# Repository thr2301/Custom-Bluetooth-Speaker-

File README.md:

# Bluetooth Speaker 

This repository contains the hardware design files and documentation for a custom Bluetooth Speaker circuit. The board integrates a lithium-ion battery management system, a boost converter, a Bluetooth audio receiver, and a Class-D audio amplifier into a single cohesive PCB. 

## Features

*   **USB-C Charging:** Modern USB Type-C receptacle for power input.
*   **Integrated Battery Management:** Onboard charging and protection circuitry for a single-cell Li-ion battery.
*   **Wireless Audio:** Integrated m18 Bluetooth module for audio streaming.
*   **High-Efficiency Audio Amplification:** Uses a Class-D amplifier capable of driving two 3W speakers.
*   **Stable 5V Power:** Integrated boost converter ensures stable 5V delivery to the audio and Bluetooth circuits regardless of battery voltage.

## Hardware Architecture

The circuit is divided into four main functional blocks:

### 1. USB-C Input & Li-ion Charger
*   Utilizes the TP4056 linear charge management controller.
*   Features dual indicator LEDs (LED_RED for charging, LED_GREEN for standby/full).
*   The USB-C input includes 5.1k pull-down resistors on the CC1 and CC2 lines to request 5V from modern USB-C PD chargers.

### 2. Battery Protection & Power Switch
*   Provides over-charge, over-discharge, and short-circuit protection using the DW01A protection IC.
*   Uses an FS8205A dual N-channel MOSFET (Q1 and Q2) to switch the battery ground.
*   Includes a physical 2-pin connector (J2) for the Li-ion battery.

### 3. 5V Boost Converter
*   Built around the MT3608 high-efficiency step-up converter.
*   A physical slide switch (SW1) sits between the battery output and the boost converter input to power the device on and off.
*   The output voltage is configured to exactly 5.0V using a feedback resistor divider (22kΩ and 3kΩ).

### 4. Audio Amplifier & Bluetooth Module
*   Powered by the PAM8403D Class-D audio amplifier.
*   Receives audio signals via the onboard m18 Bluetooth receiver module.
*   Left and Right audio channels are AC-coupled through 1uF capacitors (C7 and C9) between the Bluetooth module and the amplifier.
*   Audio output is routed to two screw terminals (J3 for Left, J4 for Right) for easy speaker connection.

## PCB Layout

The PCB layout consolidates all components onto a rectangular board. 
*   The USB-C port is edge-mounted on the left side for external access.
*   The power switch (SW1) is centrally located for user accessibility.
*   The m18 Bluetooth module is mounted on the far right edge to minimize interference with the power electronics.
*   Screw terminals for the left and right speakers are positioned along the top edge of the board.
*   The design utilizes a mix of surface-mount components (SMD) and through-hole parts (modules and connectors).

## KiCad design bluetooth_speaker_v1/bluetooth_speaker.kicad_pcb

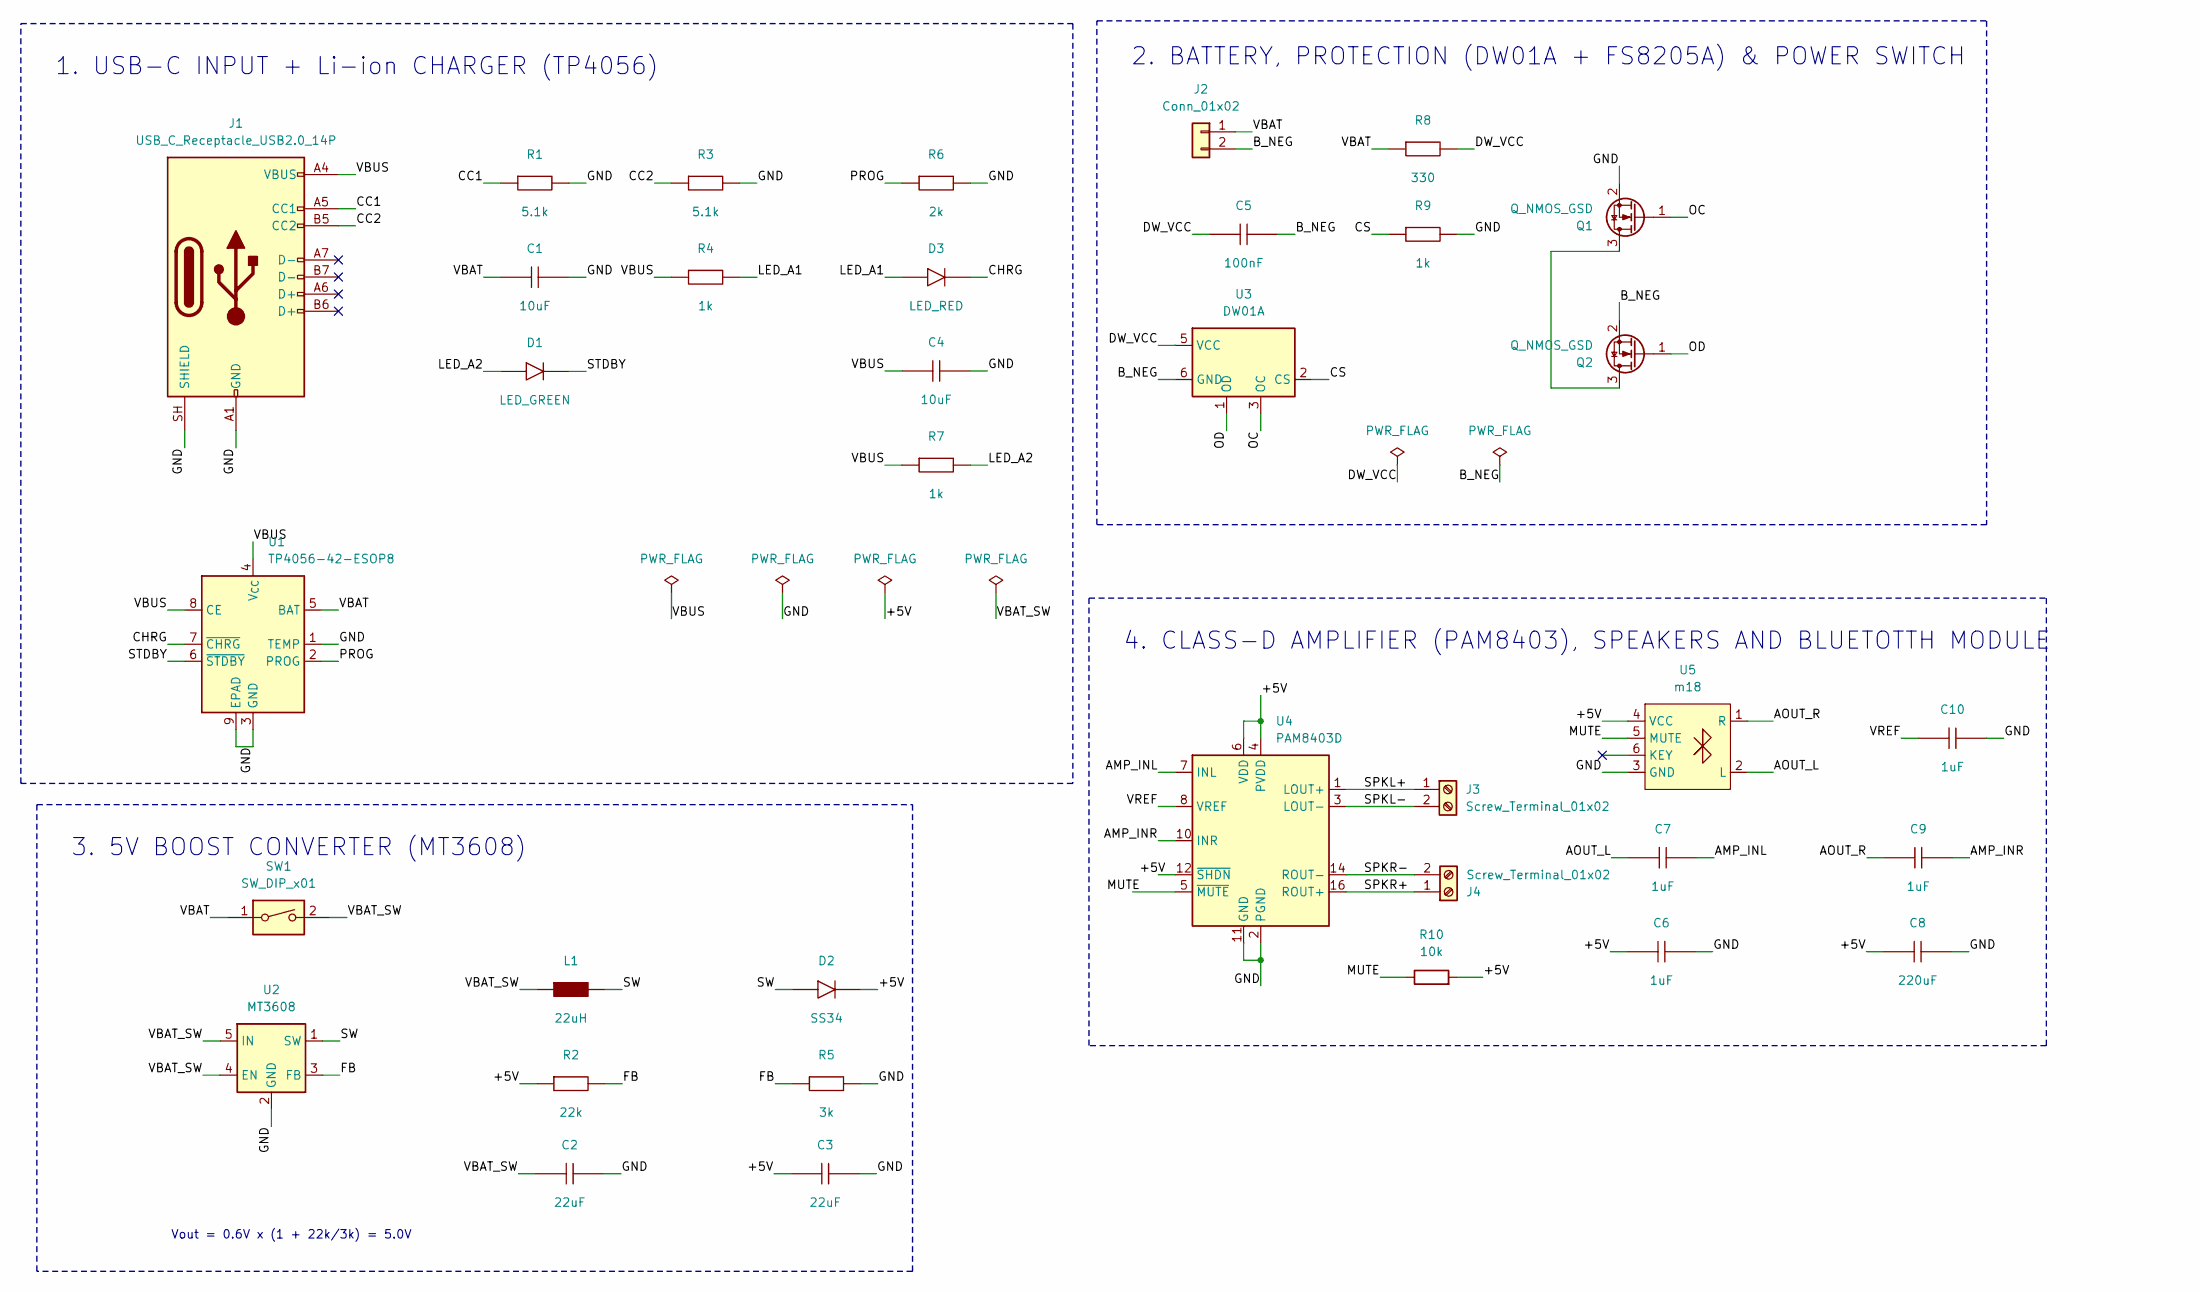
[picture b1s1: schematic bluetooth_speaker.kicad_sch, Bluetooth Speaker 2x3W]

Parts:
C1, C4: 10uF; C_0805_2012Metric
C2, C3: 22uF; C_0805_2012Metric
C5: 100nF; C_0603_1608Metric
C6, C7, C9, C10: 1uF; C_0603_1608Metric
C8: 220uF; CP_Radial_D6.3mm_P2.50mm
D1: LED_GREEN; LED_0603_1608Metric
D2: SS34; D_SMA
D3: LED_RED; LED_0603_1608Metric
J1: USB_C_Receptacle_USB2.0_14P; USB_C_Receptacle_GCT_USB4085
J2: Conn_01x02; JST_PH_B2B-PH-K_1x02_P2.00mm_Vertical
J3, J4: Screw_Terminal_01x02; TerminalBlock_Phoenix_MKDS-1,5-2-5.08_1x02_P5.08mm_Horizont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
L1: 22uH; L_1210_3225Metric
Q1, Q2: Q_NMOS_GSD; SOT-23
R1, R3: 5.1k; R_0603_1608Metric
R2: 22k; R_0603_1608Metric
R4, R7, R9: 1k; R_0603_1608Metric
R5: 3k; R_0603_1608Metric
R6: 2k; R_0603_1608Metric
R8: 330; R_0603_1608Metric
R10: 10k; R_0603_1608Metric
SW1: SW_DIP_x01; SW_DIP_SPSTx01_Slide_Copal_CHS-01A_W5.08mm_P1.27mm_JPin
U1: TP4056-42-ESOP8; SOIC-8-1EP_3.9x4.9mm_P1.27mm_EP2.41x3.3mm_ThermalVias
U2: MT3608; SOT-23-6
U3: DW01A; SOT-23-6
U4: PAM8403D; SOIC-16_3.9x9.9mm_P1.27mm
U5: m18

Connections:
/+5V: C3.1, C6.1, C8.1, D2.1, R2.1, R10.2, U4.4 (PVDD), U4.6 (VDD), U4.12 (~SHDN), U4.13 (PVDD), U5.4 (VCC)
/AMP_INL: C7.2, U4.7 (INL)
/AMP_INR: C9.2, U4.10 (INR)
/AOUT_L: C7.1, U5.2 (L)
/AOUT_R: C9.1, U5.1 (R)
/B_NEG: C5.2, J2.2, Q2.2 (S), U3.6 (GND)
/CC1: J1.A5 (CC1), R1.1
/CC2: J1.B5 (CC2), R3.1
/CHRG: D3.1, U1.7 (~CHRG)
/CS: R9.1, U3.2 (CS)
/DW_VCC: C5.1, R8.2, U3.5 (VCC)
/FB: R2.2, R5.1, U2.3 (FB)
/GND: C1.2, C2.2, C3.2, C4.2, C6.2, C8.2, C10.2, J1.A1 (GND), J1.A12 (GND), J1.B1 (GND), J1.B12 (GND), J1.SH (SHIELD), Q1.2 (S), R1.2, R3.2, R5.2, R6.2, R9.2, U1.1 (TEMP), U1.3 (GND), U1.9 (EPAD), U2.2 (GND), U4.2 (PGND), U4.11 (GND), U4.15 (PGND), U5.3 (GND)
/LED_A1: D3.2, R4.2
/LED_A2: D1.2, R7.2
/MUTE: R10.1, U4.5 (~MUTE), U5.5 (MUTE)
/OC: Q1.1 (G), U3.3 (OC)
/OD: Q2.1 (G), U3.1 (OD)
/PROG: R6.1, U1.2 (PROG)
/SPKL+: J3.1, U4.1 (LOUT+)
/SPKL-: J3.2, U4.3 (LOUT-)
/SPKR+: J4.1, U4.16 (ROUT+)
/SPKR-: J4.2, U4.14 (ROUT-)
/STDBY: D1.1, U1.6 (~STDBY)
/SW: D2.2, L1.2, U2.1 (SW)
/VBAT: C1.1, J2.1, R8.1, SW1.1, U1.5 (BAT)
/VBAT_SW: C2.1, L1.1, SW1.2, U2.4 (EN), U2.5 (IN)
/VBUS: C4.1, J1.A4 (VBUS), J1.A9 (VBUS), J1.B4 (VBUS), J1.B9 (VBUS), R4.1, R7.1, U1.4 (V_{CC}), U1.8 (CE)
/VREF: C10.1, U4.8 (VREF)
unnamed: Q1.3 (D), Q2.3 (D)

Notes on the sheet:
2. BATTERY, PROTECTION (DW01A + FS8205A) & POWER SWITCH
4. CLASS-D AMPLIFIER (PAM8403), SPEAKERS AND BLUETOTTH MODULE
1. USB-C INPUT + Li-ion CHARGER (TP4056)
3. 5V BOOST CONVERTER (MT3608)
Vout = 0.6V x (1 + 22k/3k) = 5.0V

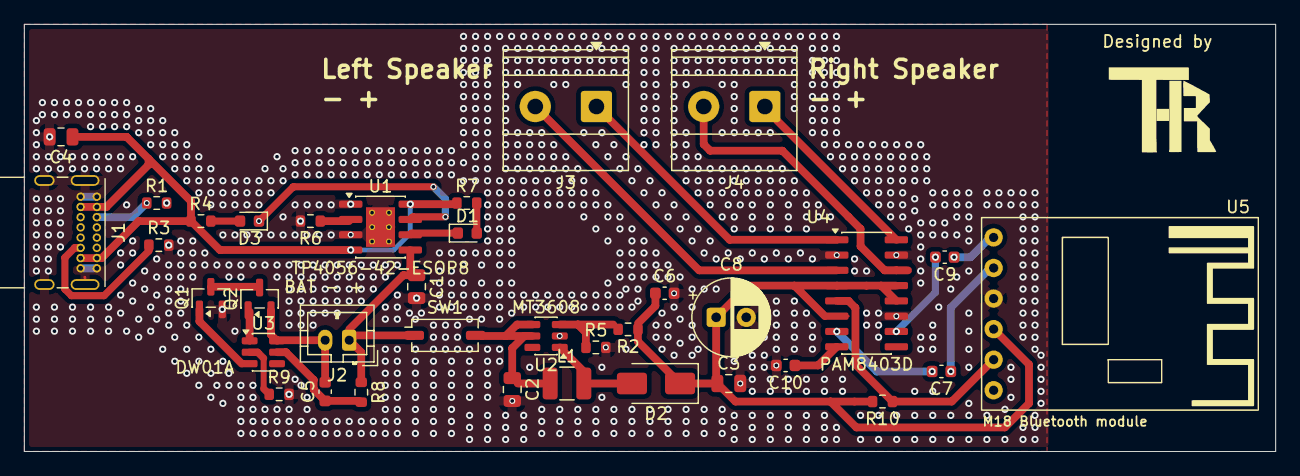
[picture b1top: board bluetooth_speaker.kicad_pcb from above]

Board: 2 copper layers, 104.0 x 35.5 mm, 36 parts (0 on the bottom side), 30 nets.
